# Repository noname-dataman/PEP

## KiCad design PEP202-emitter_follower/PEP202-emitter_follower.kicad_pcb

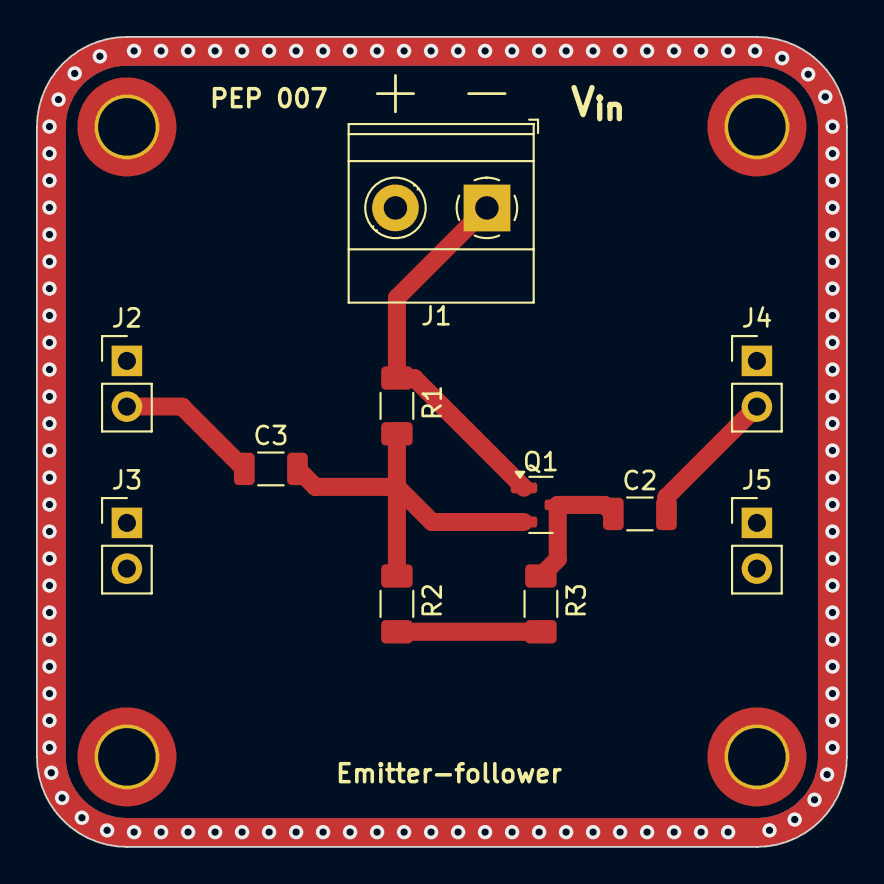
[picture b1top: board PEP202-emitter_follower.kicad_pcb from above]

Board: 2 copper layers, 45.0 x 45.0 mm, 15 parts (0 on the bottom side), 7 nets.

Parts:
C2, C3: 10u; C_1206_3216Metric
H1, H2, H3, H4: MountingHole; MountingHole_3.2mm_M3_ISO14580_Pad_TopBottom
J1: Screw_Terminal_01x02; TerminalBlock_Phoenix_MKDS-1,5-2-5.08_1x02_P5.08mm_Horizont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
J2, J3, J4, J5: Conn_01x02_Pin; PinHeader_1x02_P2.54mm_Vertical
Q1: NPN; SOT-23
R1, R2: 10k; R_smd_1206
R3: 4k7; R_smd_1206

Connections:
0: J1.2, J3.1, J3.2, J5.1, J5.2
GND: R2.2, R3.2
Input signal: C3.1, J2.1, J2.2
unnamed: C3.2, Q1.2 (B), R1.2, R2.1
unnamed: C2.1, Q1.3 (E), R3.1
Output signal: C2.2, J4.1, J4.2
Vcc: J1.1, Q1.1 (C), R1.1

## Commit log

2026-03-17 fork
